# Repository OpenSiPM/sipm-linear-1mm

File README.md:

# overview
This repository contains a 16 channel linear array detector designed for hyperspectral fluorescense imaging. Each channel is composed of a single 1x1 mm Hamamatsu S14160 SiPM mounted in a carrier board. These feed into 16 pole zero filters and 16 transimpedance amplifiers adapted from the OpenSiPM single channel design.

# pcb
The PCB is a 4 layer board that can be manufactured inexpensive (few dollars plus shipping) from a number of prototyping services. It could additionally be assembled with at least the passive components on relatively inexpensive, or it can be hand soldered via reflow. Aside from the Hamamatsdu SiPM, the components are stock at Digikey/Mouser.

[Linear array bill of materials](http://htmlpreview.github.io/?https://github.com/OpenSiPM/sipm-linear-1mm/blob/main/sipm-linear-s14160/bom/ibom.html)

# power supply
The linear sipm PCB requires a bipolar power supply capable of powering the 16 OPA847 opamps, which have about 20 mA of quescent current each on top of any output current.  This is supplied by the power-supply-linear-array project, which uses two sets of linear and negative regulators combined with a charge pump to generate the required currents. 

[Power supply bill of materials](http://htmlpreview.github.io/?https://github.com/OpenSiPM/sipm-linear-1mm/blob/main/power-supply-linear-array/kicad/bom/ibom.html)

# bias generator
The bias generator provides the high voltage (~49V) required to bias the SPAD cells in the SiPM. Two versions are provided, a standard one using USB-C and a modified one with a second USB-C connector that allows connecting to an external USB-C power supply.  This can be useful as the total array power is about 3W, and so exceeds the 2.5W supplied by USB2 devices.  By using the second port, the power per port can be kept under 500 mA for hubs and hosts that are not USB3 or USB-C.  

[Power supply bill of materials](http://htmlpreview.github.io/?https://github.com/OpenSiPM/sipm-linear-1mm/blob/main/bias-control-lt8364-linear/bom/ibom.html)

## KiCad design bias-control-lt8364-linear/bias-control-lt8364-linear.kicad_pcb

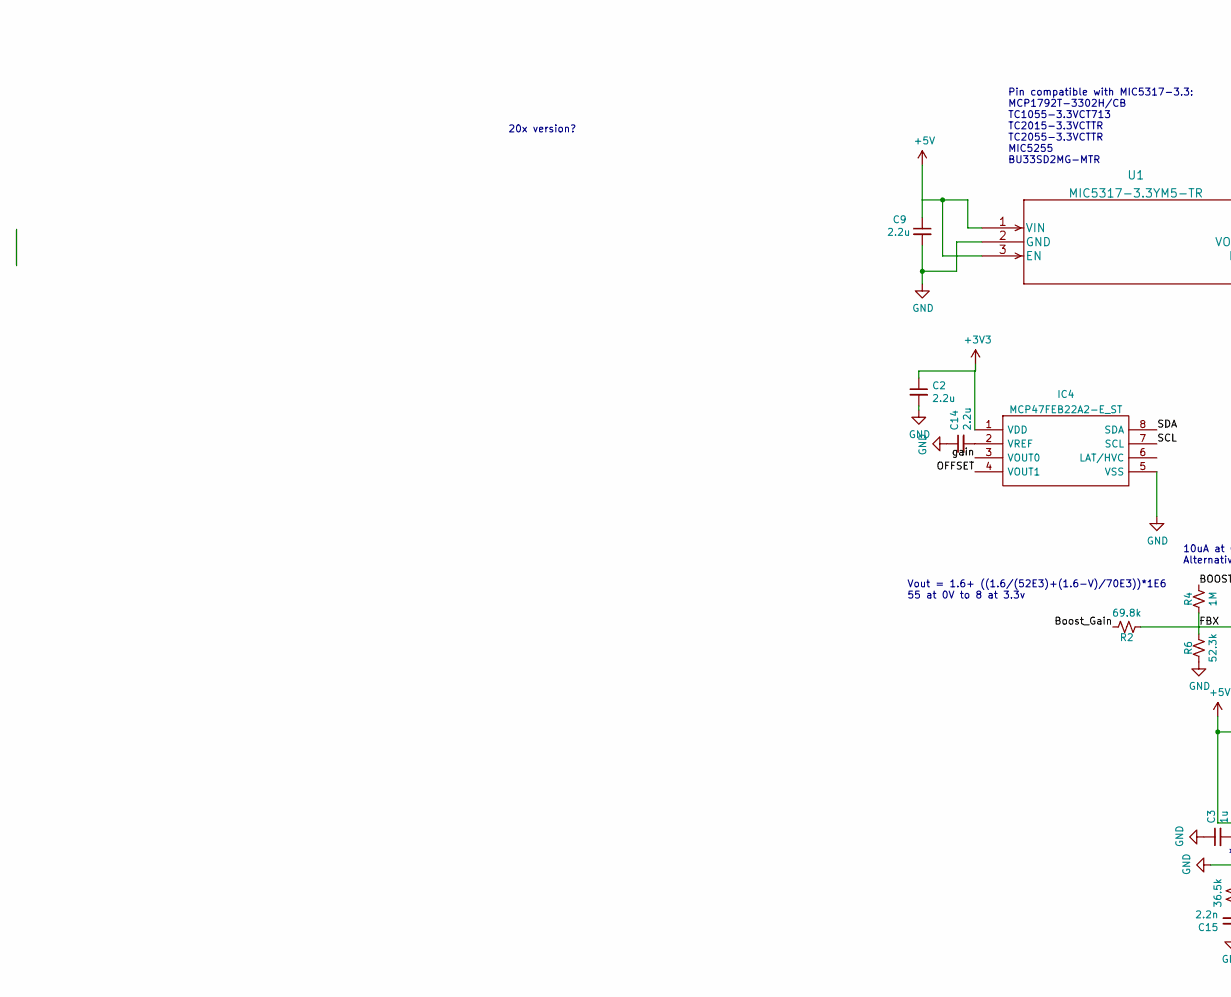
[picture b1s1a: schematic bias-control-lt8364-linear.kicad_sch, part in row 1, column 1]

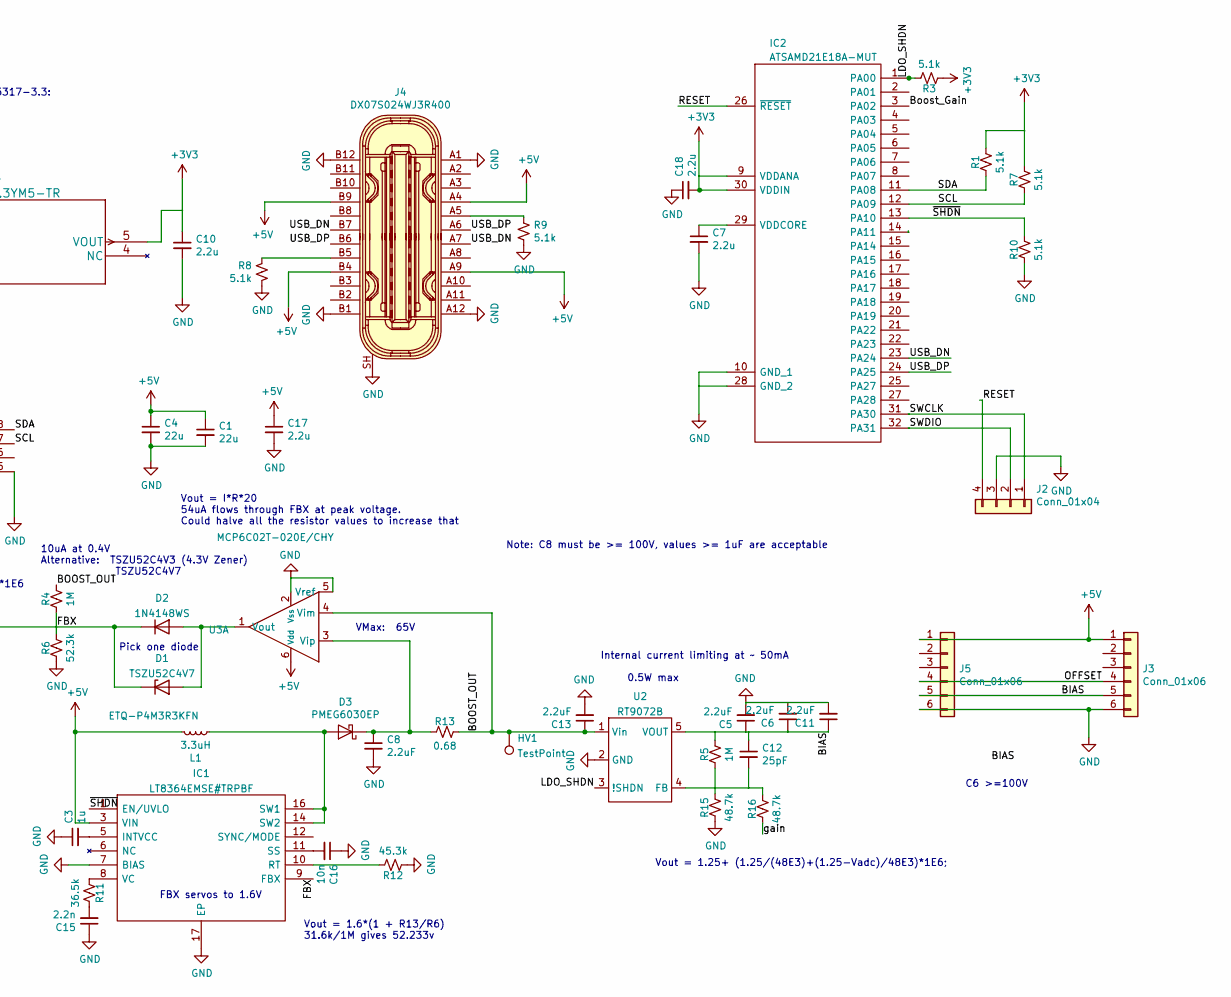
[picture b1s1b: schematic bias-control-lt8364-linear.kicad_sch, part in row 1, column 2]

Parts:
C1, C4: 22u; C_0603_1608Metric; Voltage 10V
C2, C7, C9, C10, C14, C17, C18: 2.2u; C_0402_1005Metric
C3: 1u; C_0402_1005Metric
C5, C6, C8, C11, C13: 2.2uF; C_1206_3216Metric; Voltage 100V
C12: 25pF; C_0402_1005Metric
C15: 2.2n; C_0402_1005Metric
C16: 10n; C_0402_1005Metric
D1: TSZU52C4V7; D_0603_1608Metric
D2: 1N4148WS; D_SOD-323F
D3: PMEG6030EP; D_SOD-128
HV1: TestPoint; TestPoint_Pad_D1.0mm
IC1: LT8364EMSE#TRPBF; LT8364IMSE-PBF; Mouser Part Number 584-LT8364EMSETRPBF
IC2: ATSAMD21E18A-MUT; QFN-32-1EP_5x5mm_Pitch0.5mm; Manufacturer_Part_Number ATSAMD21E18A-AFT
IC4: MCP47FEB22A2-E_ST; SOP65P640X120-8N; Mouser Part Number 579-MCP47FEB22A2EST
J2: Conn_01x04; PinHeader_1x04_P2.54mm_Vertical_SMD_Pin1Right
J3, J5: Conn_01x06; PinHeader_2x03_P2.54mm_Vertical
J4: DX07S024WJ3R400; USB-C_Female_Vert_DX07S024WJ3R400; MPN DX07S024WJ3R400; Digi-Key_PN 670-2950-1-ND
L1: 3.3uH; IND_ETQP4M3R3KFN; MPN ETQ-P4M3R3KFN
R1, R3, R7, R8, R9, R10: 5.1k; R_0402_1005Metric
R2: 69.8k; R_0402_1005Metric
R4, R5: 1M; R_0402_1005Metric
R6: 52.3k; R_0402_1005Metric
R11: 36.5k; R_0402_1005Metric
R12: 45.3k; R_0402_1005Metric
R13: 0.68; R_0402_1005Metric
R15, R16: 48.7k; R_0402_1005Metric
U1: MIC5317-3.3YM5-TR
U2: RT9072B; SOT-23-5
U3: MCP6C02T-020E/CHY; SOT-23-6

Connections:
+3V3: C2.1, C10.1, C18.2, IC2.9 (VDDANA), IC2.30 (VDDIN), IC4.1 (VDD), R1.1, R3.2, R7.1, U1.5 (VOUT)
+5V: C1.1, C4.1, C9.1, C17.1, IC1.3 (VIN), J3.1, J4.A4, J4.A9, J4.B4, J4.B9, J5.1, L1.2, U1.1 (VIN), U1.3 (EN), U3.6 (Vdd)
/BIAS: C5.1, C6.1, C11.1, C12.1, J3.5, J5.5, R5.1, U2.5 (VOUT)
/BOOST_OUT: C13.1, HV1.1, R4.1, R13.1, U2.1 (Vin), U3.4 (Vim)
/Boost_Gain: IC2.3 (PA02), R2.1
/FBX: D1.1 (K), D2.1 (K), IC1.9 (FBX), R2.2, R4.2, R6.1
/LDO_SHDN: IC2.1 (PA00), R3.1, U2.3 (!SHDN)
/OFFSET: IC4.4 (VOUT1), J3.4, J5.4
/RESET: IC2.26 (~RESET), J2.4
/SCL: IC2.12 (PA09), IC4.7 (SCL), R7.2
/SDA: IC2.11 (PA08), IC4.8 (SDA), R1.2
/SWCLK: IC2.31 (PA30), J2.1
/SWDIO: IC2.32 (PA31), J2.2
/USB_DN: IC2.23 (PA24), J4.A7, J4.B7
/USB_DP: IC2.24 (PA25), J4.A6, J4.B6
/gain: IC4.3 (VOUT0), R16.2
/~SHDN: IC1.1 (EN/UVLO), IC2.13 (PA10), R10.1
GND: C1.2, C2.2, C3.1, C4.2, C5.2, C6.2, C7.2, C8.2, C9.2, C10.2, C11.2, C13.2, C14.1, C15.1, C16.1, C17.2, C18.1, IC1.7 (BIAS), IC1.17 (EP), IC2.10 (GND_1), IC2.28 (GND_2), IC2.33 (EP), IC4.5 (VSS), J2.3, J3.6, J4.A1, J4.A12, J4.B1, J4.B12, J4.SH, J5.6, R6.2, R8.2, R9.2, R10.2, R12.2, R15.2, U1.2 (GND), U2.2 (GND), U3.2 (Vss), U3.5 (Vref)
unnamed: C15.2, R11.1
unnamed: D1.2 (A), D2.2 (A), U3.1 (Vout)
unnamed: D3.2 (A), IC1.14 (SW2), IC1.16 (SW1), L1.1
unnamed: C8.1, D3.1 (K), R13.2, U3.3 (Vip)
unnamed: C3.2, IC1.5 (INTVCC)
unnamed: IC1.10 (RT), R12.1
unnamed: C16.2, IC1.11 (SS)
unnamed: IC1.8 (VC), R11.2
unnamed: C7.1, IC2.29 (VDDCORE)
unnamed: C14.2, IC4.2 (VREF)
unnamed: J4.A5, R9.1
unnamed: J4.B5, R8.1
unnamed: C12.2, R5.2, R15.1, R16.1, U2.4 (FB)

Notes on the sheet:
Vout = 1.6*(1 + R13/R6) 31.6k/1M gives 52.233v
Note: C8 must be >= 100V, values >= 1uF are acceptable
Vout = I*R*20 54uA flows through FBX at peak voltage. Could halve all the resistor values to increase that
Pick one diode
Internal current limiting at ~ 50mA
Pin compatible with MIC5317-3.3: MCP1792T-3302H/CB TC1055-3.3VCT713 TC2015-3.3VCTTR TC2055-3.3VCTTR MIC5255 BU33SD2MG-MTR
20x version?
0.5W max
10uA at 0.4V Alternative: TSZU52C4V3 (4.3V Zener) TSZU52C4V7
C6 >=100V
Vout = 1.25+ (1.25/(48E3)+(1.25-Vadc)/48E3)*1E6;
VMax: 65V
Vout = 1.6+ ((1.6/(52E3)+(1.6-V)/70E3))*1E6 55 at 0V to 8 at 3.3v
FBX servos to 1.6V

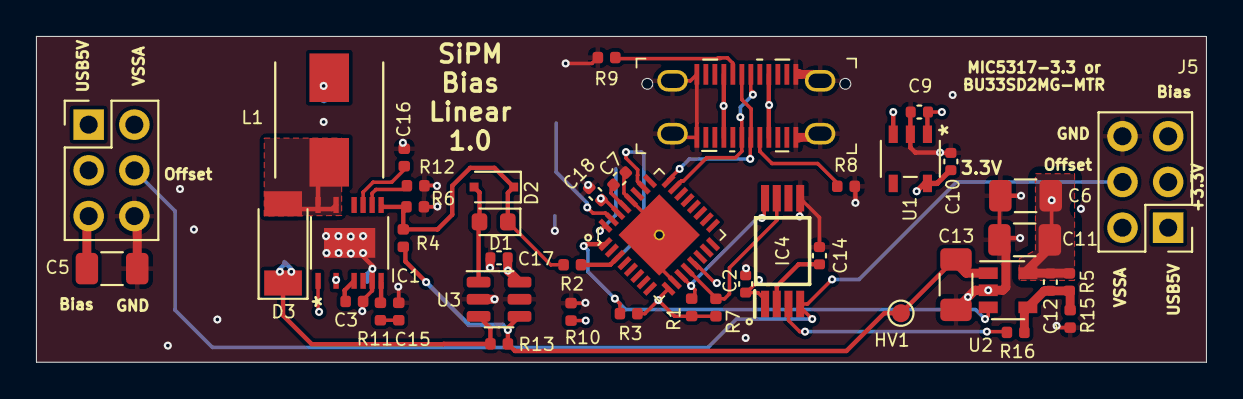
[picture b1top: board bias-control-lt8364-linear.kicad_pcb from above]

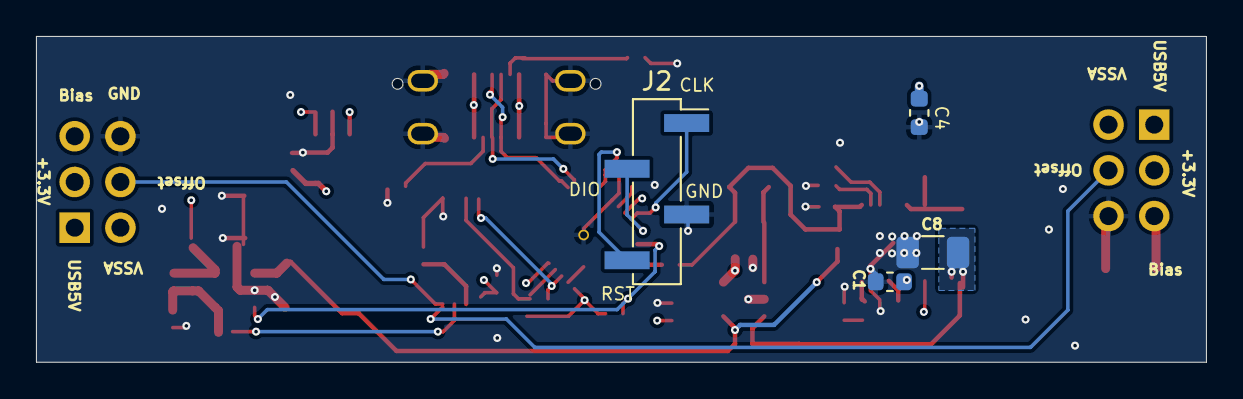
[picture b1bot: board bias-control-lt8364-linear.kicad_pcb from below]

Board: 4 copper layers, 65.0 x 18.1 mm, 48 parts (4 on the bottom side), 31 nets.

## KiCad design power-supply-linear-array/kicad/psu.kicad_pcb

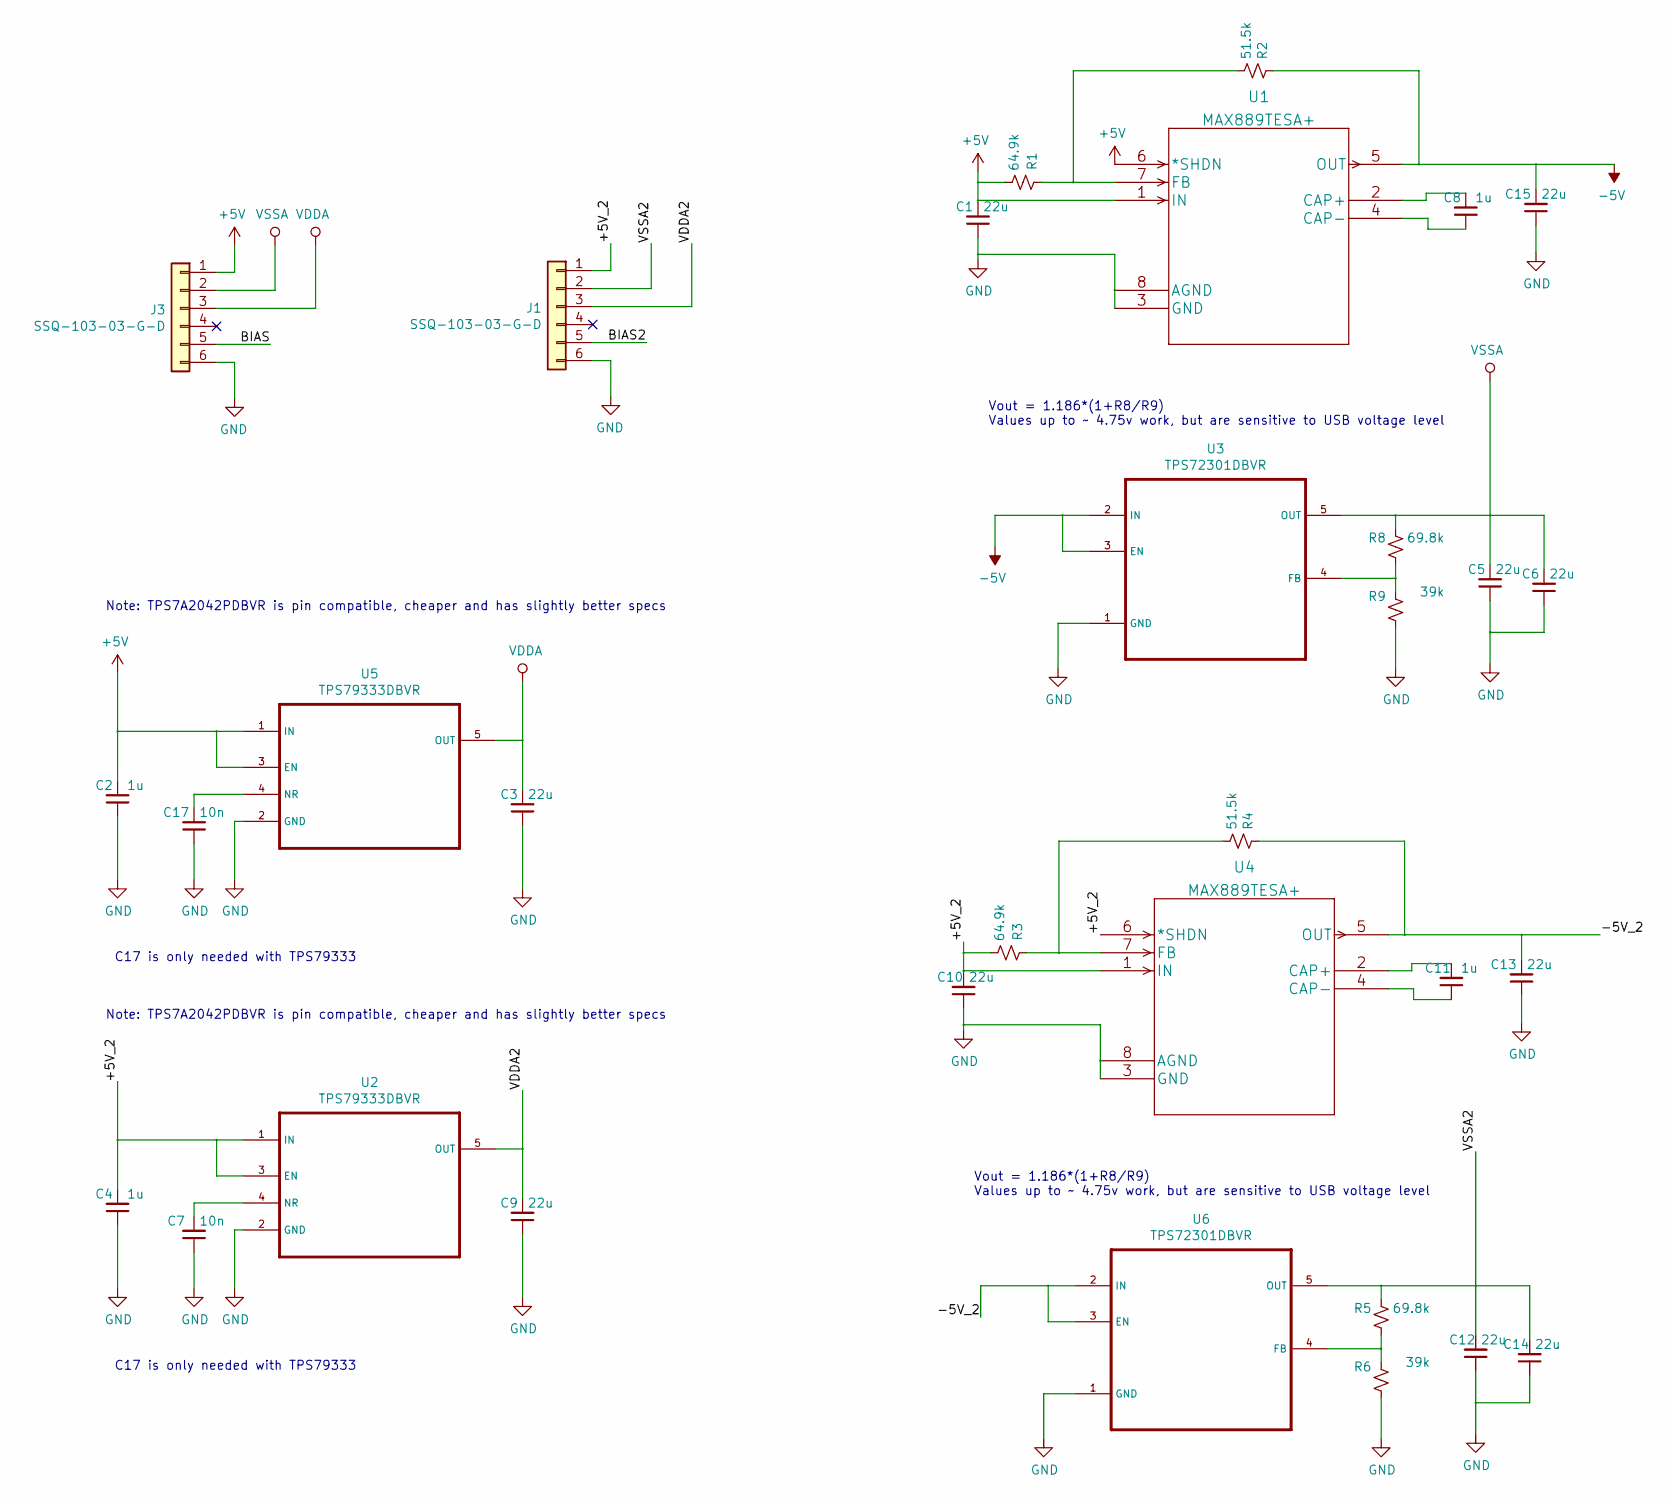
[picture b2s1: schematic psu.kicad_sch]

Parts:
C1, C3, C5, C6, C9, C10, C12, C13, C14, C15: 22u; C_0603_1608Metric
C2, C4, C8, C11: 1u; C_0603_1608Metric
C7, C17: 10n; C_0603_1608Metric
J1, J3: SSQ-103-03-G-D; PinHeader_2x03_P2.54mm_Vertical
R1, R3: 64.9k; R_0603_1608Metric
R2, R4: 51.5k; R_0603_1608Metric
R5, R8: 69.8k; R_0603_1608Metric
R6, R9: 39k; R_0603_1608Metric
U1, U4: MAX889TESA+; MAX889TESA&plus_
U2, U5: TPS79333DBVR
U3, U6: TPS72301DBVR

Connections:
+5V: C1.2, C2.2, J3.1, R1.2, U1.1 (IN), U1.6 (*SHDN), U5.1 (IN), U5.3 (EN)
-5V: C15.2, R2.1, U1.5 (OUT), U3.2 (IN), U3.3 (EN)
/+5V_2: C4.2, C10.2, J1.1, R3.2, U2.1 (IN), U2.3 (EN), U4.1 (IN), U4.6 (*SHDN)
/-5V_2: C13.2, R4.1, U4.5 (OUT), U6.2 (IN), U6.3 (EN)
/BIAS: J3.5
/BIAS2: J1.5
/VDDA2: C9.2, J1.3, U2.5 (OUT)
/VSSA2: C12.2, C14.2, J1.2, R5.2, U6.5 (OUT)
GND: C1.1, C2.1, C3.1, C4.1, C5.1, C6.1, C7.1, C9.1, C10.1, C12.1, C13.1, C14.1, C15.1, C17.1, J1.6, J3.6, R6.1, R9.1, U1.3 (GND), U1.8 (AGND), U2.2 (GND), U3.1 (GND), U4.3 (GND), U4.8 (AGND), U5.2 (GND), U6.1 (GND)
unnamed: C8.2, U1.2 (CAP+)
unnamed: C8.1, U1.4 (CAP-)
unnamed: R1.1, R2.2, U1.7 (FB)
unnamed: C7.2, U2.4 (NR)
unnamed: R8.1, R9.2, U3.4 (FB)
unnamed: C11.2, U4.2 (CAP+)
unnamed: C11.1, U4.4 (CAP-)
unnamed: R3.1, R4.2, U4.7 (FB)
unnamed: C17.2, U5.4 (NR)
unnamed: R5.1, R6.2, U6.4 (FB)
VDDA: C3.2, J3.3, U5.5 (OUT)
VSSA: C5.2, C6.2, J3.2, R8.2, U3.5 (OUT)

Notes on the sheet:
Vout = 1.186*(1+R8/R9) Values up to ~ 4.75v work, but are sensitive to USB voltage level
Note: TPS7A2042PDBVR is pin compatible, cheaper and has slightly better specs
C17 is only needed with TPS79333

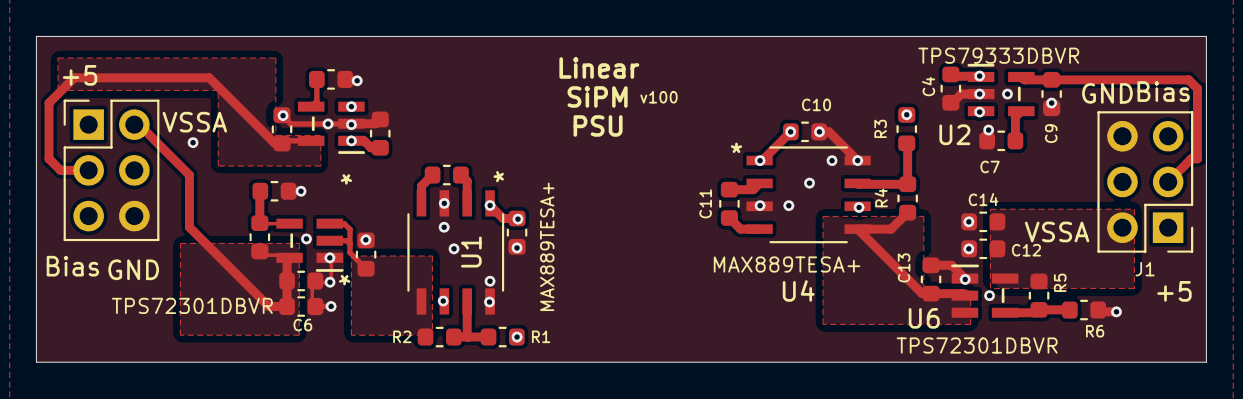
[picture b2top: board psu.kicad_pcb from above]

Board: 4 copper layers, 65.0 x 18.1 mm, 32 parts (0 on the bottom side), 19 nets.

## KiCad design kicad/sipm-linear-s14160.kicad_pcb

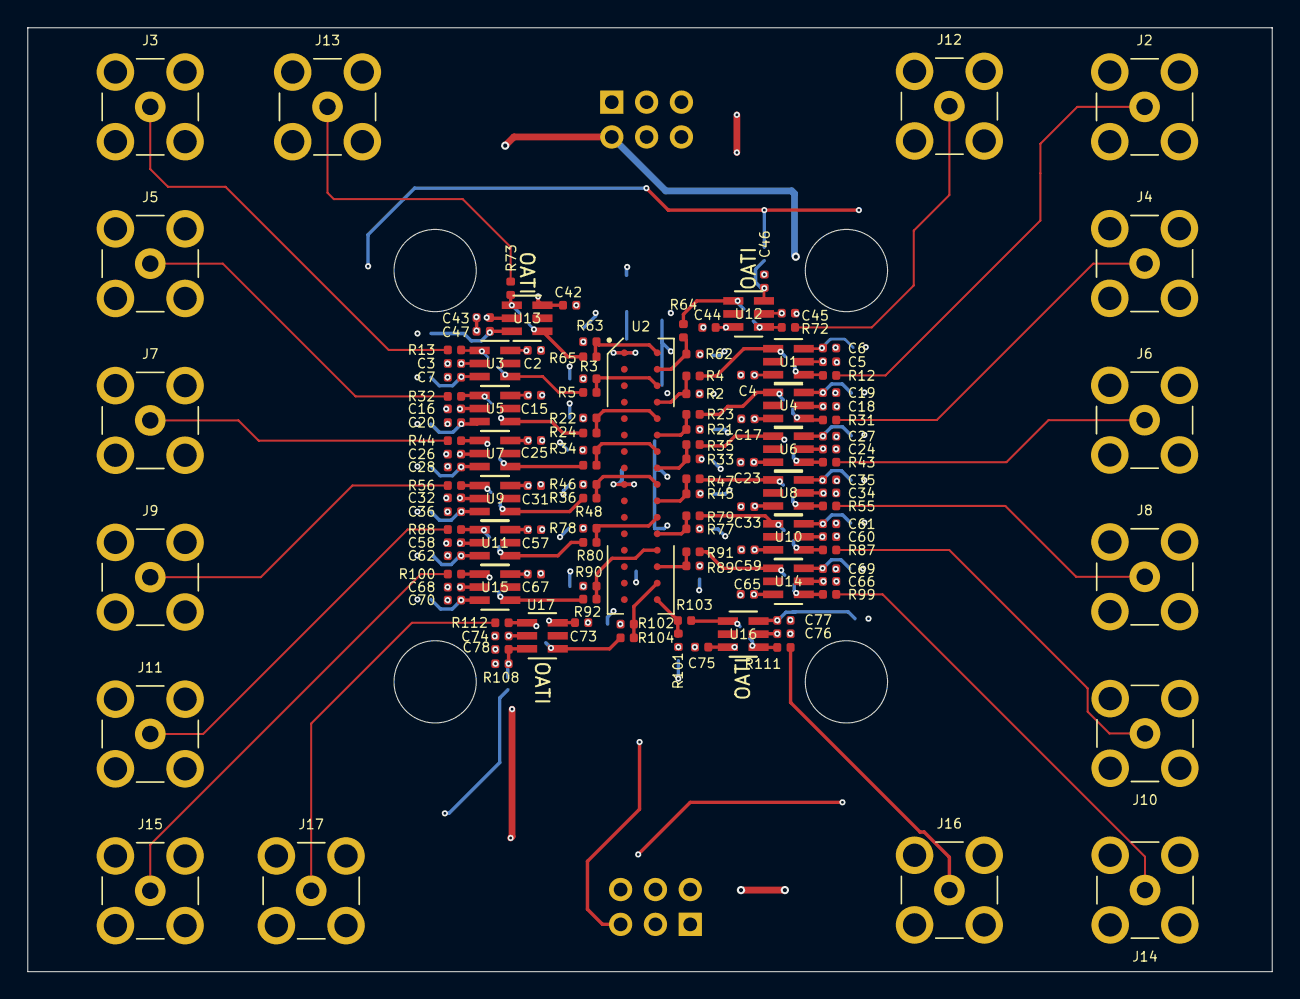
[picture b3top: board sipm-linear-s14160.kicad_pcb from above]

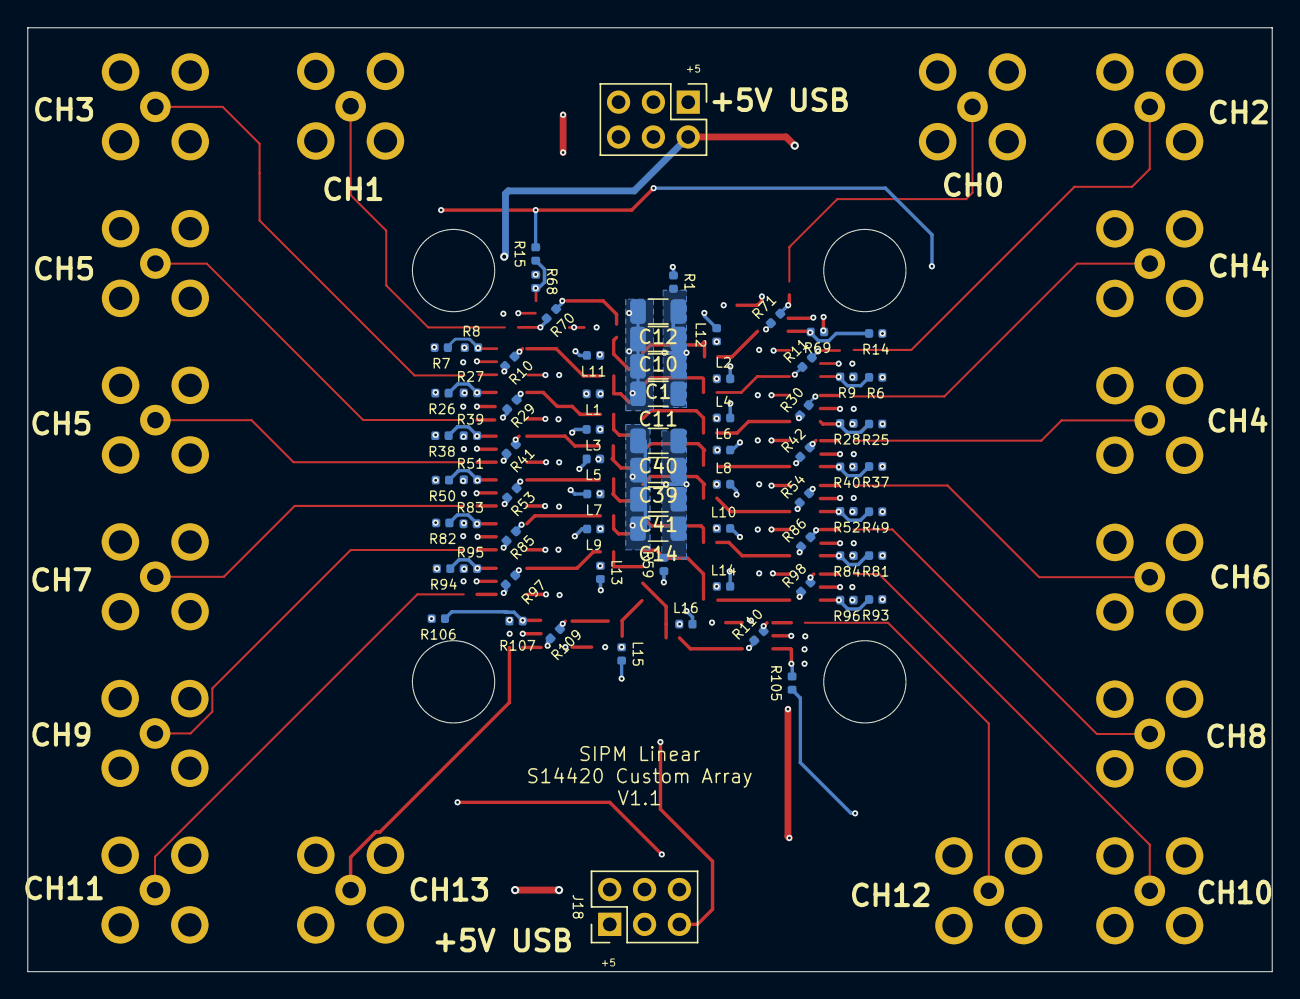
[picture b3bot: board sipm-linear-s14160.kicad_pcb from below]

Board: 4 copper layers, 90.8 x 68.9 mm, 209 parts (75 on the bottom side), 107 nets.

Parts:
C1, C10, C11, C12, C14, C39, C40, C41: 1u; C_1206_3216Metric
C2, C3, C4, C5, C6, C7, C15, C16, C17, C18, C19, C20, C23, C24, C25, C26, C27, C28, C31, C32, C33, C34, C35, C36, C42, C43, C44, C45, C46, C47, C57, C58, C59, C60, C61, C62, C65, C66, C67, C68, C69, C70, C73, C74, C75, C76, C77, C78: 1u; C_0402_1005Metric
H1, H2, H3, H4: MountingHole; MountingHole_6mm
J1, J18: SSQ-103-01-G-D; PinHeader_2x03_P2.54mm_Vertical
J2, J3, J4, J5, J6, J7, J8, J9, J10, J11, J12, J13, J14, J15, J16, J17: Conn_Coaxial; SMB_Jack_Vertical
L1, L2, L3, L4, L5, L6, L7, L8, L9, L10, L11, L12, L13, L14, L15, L16: 0.090uH; C_0402_1005Metric
R1, R59: 10; R_0402_1005Metric
R2, R3, R21, R22, R33, R34, R45, R46, R62, R63, R77, R78, R89, R90, R101, R102: 6.3; R_0402_1005Metric
R4, R5, R23, R24, R35, R36, R47, R48, R64, R65, R79, R80, R91, R92, R103, R104: 43; R_0402_1005Metric
R6, R7, R14, R15, R25, R26, R37, R38, R49, R50, R81, R82, R93, R94, R105, R106: 5000; R_0402_1005Metric
R8, R9, R27, R28, R39, R40, R51, R52, R68, R69, R83, R84, R95, R96, R107, R108: 68; R_0402_1005Metric
R10, R11, R29, R30, R41, R42, R53, R54, R70, R71, R85, R86, R97, R98, R109, R110: 1.5k; R_0402_1005Metric
R12, R13, R31, R32, R43, R44, R55, R56, R72, R73, R87, R88, R99, R100, R111, R112: 50; R_0402_1005Metric
U1, U3, U4, U5, U6, U7, U8, U9, U10, U11, U12, U13, U14, U15, U16, U17: OPA847IDBVT
U2: S15643; AF210729-S14160-x16

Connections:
/LINE2: J18.4, R49.1, R50.2, R81.1, R82.2, R93.1, R94.2, R105.1, R106.2
/SipmPair1/IN1: R3.2, R5.1, U2.6 (3A)
/SipmPair1/IN2: R2.2, R4.1, U2.8 (4A)
/SipmPair2/IN1: R22.2, R24.1, U2.10 (5A)
/SipmPair2/IN2: R21.2, R23.1, U2.12 (6A)
/SipmPair3/IN1: R34.2, R36.1, U2.14 (7A)
/SipmPair3/IN2: R33.2, R35.1, U2.16 (8A)
/SipmPair4/IN1: R46.2, R48.1, U2.18 (9A)
/SipmPair4/IN2: R45.2, R47.1, U2.20 (10A)
/SipmPair5/IN1: R78.2, R80.1, U2.22 (11A)
/SipmPair5/IN2: R77.2, R79.1, U2.24 (12A)
/SipmPair6/IN1: R90.2, R92.1, U2.26 (13A)
/SipmPair6/IN2: R89.2, R91.1, U2.28 (14A)
/SipmPair7/IN1: R102.2, R104.1, U2.30 (15A)
/SipmPair7/IN2: R101.2, R103.1, U2.32 (16A)
/SipmPair/IN1: R63.2, R65.1, U2.2 (1A)
/SipmPair/IN2: R62.2, R64.1, U2.4 (2A)
/VBias: J1.5, R1.1
/VBias2: J18.5, R59.1
/VDDA2: C31.1, C33.1, C57.1, C59.1, C65.1, C67.1, C73.1, C75.1, J18.3, U8.6 (V+), U9.6 (V+), U10.6 (V+), U11.6 (V+), U14.6 (V+), U15.6 (V+), U16.6 (V+), U17.6 (V+)
/VSSA2: C32.1, C34.1, C58.1, C60.1, C66.1, C68.1, C74.1, C76.1, J18.2, U8.2 (V-), U9.2 (V-), U10.2 (V-), U11.2 (V-), U14.2 (V-), U15.2 (V-), U16.2 (V-), U17.2 (V-)
GND: C1.2, C2.2, C3.2, C4.2, C5.2, C6.2, C7.2, C10.2, C11.2, C12.2, C14.2, C15.2, C16.2, C17.2, C18.2, C19.2, C20.2, C23.2, C24.2, C25.2, C26.2, C27.2, C28.2, C31.2, C32.2, C33.2, C34.2, C35.2, C36.2, C39.2, C40.2, C41.2, C42.2, C43.2, C44.2, C45.2, C46.2, C47.2, C57.2, C58.2, C59.2, C60.2, C61.2, C62.2, C65.2, C66.2, C67.2, C68.2, C69.2, C70.2, C73.2, C74.2, C75.2, C76.2, C77.2, C78.2, J1.6, J2.2 (Ext), J3.2 (Ext), J4.2 (Ext), J5.2 (Ext), J6.2 (Ext), J7.2 (Ext), J8.2 (Ext), J9.2 (Ext), J10.2 (Ext), J11.2 (Ext), J12.2 (Ext), J13.2 (Ext), J14.2 (Ext), J15.2 (Ext), J16.2 (Ext), J17.2 (Ext), J18.6, L1.2, L2.2, L3.2, L4.2, L5.2, L6.2, L7.2, L8.2, L9.2, L10.2, L11.2, L12.2, L13.2, L14.2, L15.2, L16.2, R8.1, R9.1, R27.1, R28.1, R39.1, R40.1, R51.1, R52.1, R68.1, R69.1, R83.1, R84.1, R95.1, R96.1, R107.1, R108.1
LINE: J1.4, R6.1, R7.2, R14.1, R15.2, R25.1, R26.2, R37.1, R38.2
unnamed: J2.1 (In), R12.2
unnamed: J3.1 (In), R13.2
unnamed: J4.1 (In), R31.2
unnamed: J5.1 (In), R32.2
unnamed: J6.1 (In), R43.2
unnamed: J7.1 (In), R44.2
unnamed: J8.1 (In), R55.2
unnamed: J9.1 (In), R56.2
unnamed: J10.1 (In), R87.2
unnamed: J11.1 (In), R88.2
unnamed: J12.1 (In), R72.2
unnamed: J13.1 (In), R73.2
unnamed: J14.1 (In), R99.2
unnamed: J15.1 (In), R100.2
unnamed: J16.1 (In), R111.2
unnamed: J17.1 (In), R112.2
unnamed: L1.1, R2.1
unnamed: L2.1, R3.1
unnamed: L3.1, R21.1
unnamed: L4.1, R22.1
unnamed: L5.1, R33.1
unnamed: L6.1, R34.1
unnamed: L7.1, R45.1
unnamed: L8.1, R46.1
unnamed: L9.1, R77.1
unnamed: L10.1, R78.1
unnamed: L11.1, R62.1
unnamed: L12.1, R63.1
unnamed: L13.1, R89.1
unnamed: L14.1, R90.1
unnamed: L15.1, R101.1
unnamed: L16.1, R102.1
unnamed: R10.2, R12.1, U1.1
unnamed: R11.2, R13.1, U3.1
unnamed: R29.2, R31.1, U4.1
unnamed: R30.2, R32.1, U5.1
unnamed: R41.2, R43.1, U6.1
unnamed: R42.2, R44.1, U7.1
unnamed: R53.2, R55.1, U8.1
unnamed: R54.2, R56.1, U9.1
unnamed: R70.2, R72.1, U12.1
unnamed: R71.2, R73.1, U13.1
unnamed: R85.2, R87.1, U10.1
unnamed: R86.2, R88.1, U11.1
unnamed: R97.2, R99.1, U14.1
unnamed: R98.2, R100.1, U15.1
unnamed: R109.2, R111.1, U16.1
unnamed: R110.2, R112.1, U17.1
unnamed: C6.1, R7.1, R8.2, U1.3 (+)
unnamed: R4.2, R10.1, U1.4 (-)
unnamed: C1.1, C10.1, C11.1, C12.1, R1.2, U2.1 (1K)
unnamed: C14.1, C39.1, C40.1, C41.1, R59.2, U2.17 (9K)
unnamed: C7.1, R6.2, R9.2, U3.3 (+)
unnamed: R5.2, R11.1, U3.4 (-)
unnamed: C19.1, R26.1, R27.2, U4.3 (+)
unnamed: R23.2, R29.1, U4.4 (-)
unnamed: C20.1, R25.2, R28.2, U5.3 (+)
unnamed: R24.2, R30.1, U5.4 (-)
unnamed: C27.1, R38.1, R39.2, U6.3 (+)
unnamed: R35.2, R41.1, U6.4 (-)
unnamed: C28.1, R37.2, R40.2, U7.3 (+)
unnamed: R36.2, R42.1, U7.4 (-)
unnamed: C35.1, R50.1, R51.2, U8.3 (+)
unnamed: R47.2, R53.1, U8.4 (-)
unnamed: C36.1, R49.2, R52.2, U9.3 (+)
unnamed: R48.2, R54.1, U9.4 (-)
unnamed: C61.1, R82.1, R83.2, U10.3 (+)
unnamed: R79.2, R85.1, U10.4 (-)
unnamed: C62.1, R81.2, R84.2, U11.3 (+)
unnamed: R80.2, R86.1, U11.4 (-)
unnamed: C46.1, R15.1, R68.2, U12.3 (+)
unnamed: R64.2, R70.1, U12.4 (-)
unnamed: C47.1, R14.2, R69.2, U13.3 (+)
unnamed: R65.2, R71.1, U13.4 (-)
unnamed: C69.1, R94.1, R95.2, U14.3 (+)
unnamed: R91.2, R97.1, U14.4 (-)
unnamed: C70.1, R93.2, R96.2, U15.3 (+)
unnamed: R92.2, R98.1, U15.4 (-)
unnamed: C77.1, R106.1, R107.2, U16.3 (+)
unnamed: R103.2, R109.1, U16.4 (-)
unnamed: C78.1, R105.2, R108.2, U17.3 (+)
unnamed: R104.2, R110.1, U17.4 (-)
VDDA: C2.1, C4.1, C15.1, C17.1, C23.1, C25.1, C42.1, C44.1, J1.3, U1.6 (V+), U3.6 (V+), U4.6 (V+), U5.6 (V+), U6.6 (V+), U7.6 (V+), U12.6 (V+), U13.6 (V+)
VSSA: C3.1, C5.1, C16.1, C18.1, C24.1, C26.1, C43.1, C45.1, J1.2, U1.2 (V-), U3.2 (V-), U4.2 (V-), U5.2 (V-), U6.2 (V-), U7.2 (V-), U12.2 (V-), U13.2 (V-)

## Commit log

2021-08-30 Initial check in of the S15643 linear design files before adapting for the revised S14160 design
2021-08-30 Update layout for the new footprint
2021-10-06 Update layout and fix array footprint
2021-10-06 Update foot print for the revised hamamatsu part
    They only have 2 cathode connections. In addition, add a second power connector, since at least two power supplies are going to be needed.
2021-10-07 Add step model for the sipm array
2021-10-07 Split power rails across two power supplies
2022-01-29 Rename to reflect that we are using the s14160 elements in the array
2022-01-31 Check in before removing feedback cap
2022-02-08 First version that passes schematic parity check
2022-02-08 Near final version
    Sorted out the line input, flipped the connectors around to the correct board side and cleaned up the silkscreen.
2022-06-09 Update the PCB with final PZC and offset values
    In testing, the PZC worked well with 6.3/43/90nH on the S14160-1315 which we are assuming is very similar. These values may not be quite right for the array but are hopefully close. The 68/5000 ohm o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
2022-07-28 Check in sipm linear manufacturing files
2022-07-28 Change decoupling to 1206
2024-09-20 Fix track under drill hole
    Pretty sure JLCPCB quietly fixed this for us on the initial design.
2024-09-20 Remove old file
2024-09-21 Check in more changes
    Forgot to hit save before last commits.
2024-09-21 Add README.md
2024-09-21 Remove old gerbers
    Don't use these, they aren't the final design.
2024-09-21 Rename project folder
2024-09-21 Add power supplies and bias generator
    Note there are two power supply models, a base one and one that can take power from a second USB device to stay under the 500 mA USB2 limit (works fine on USB3 or USB-C hosts).
2024-09-21 Update power supply board for latest kicad
    Silence a bunch of unimportant DRC warnings.

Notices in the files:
parts and their libraries:
Copyright 2021 Accelerated Designs. All rights reserved.
Copyright 2016 Accelerated Designs. All rights reserved.
